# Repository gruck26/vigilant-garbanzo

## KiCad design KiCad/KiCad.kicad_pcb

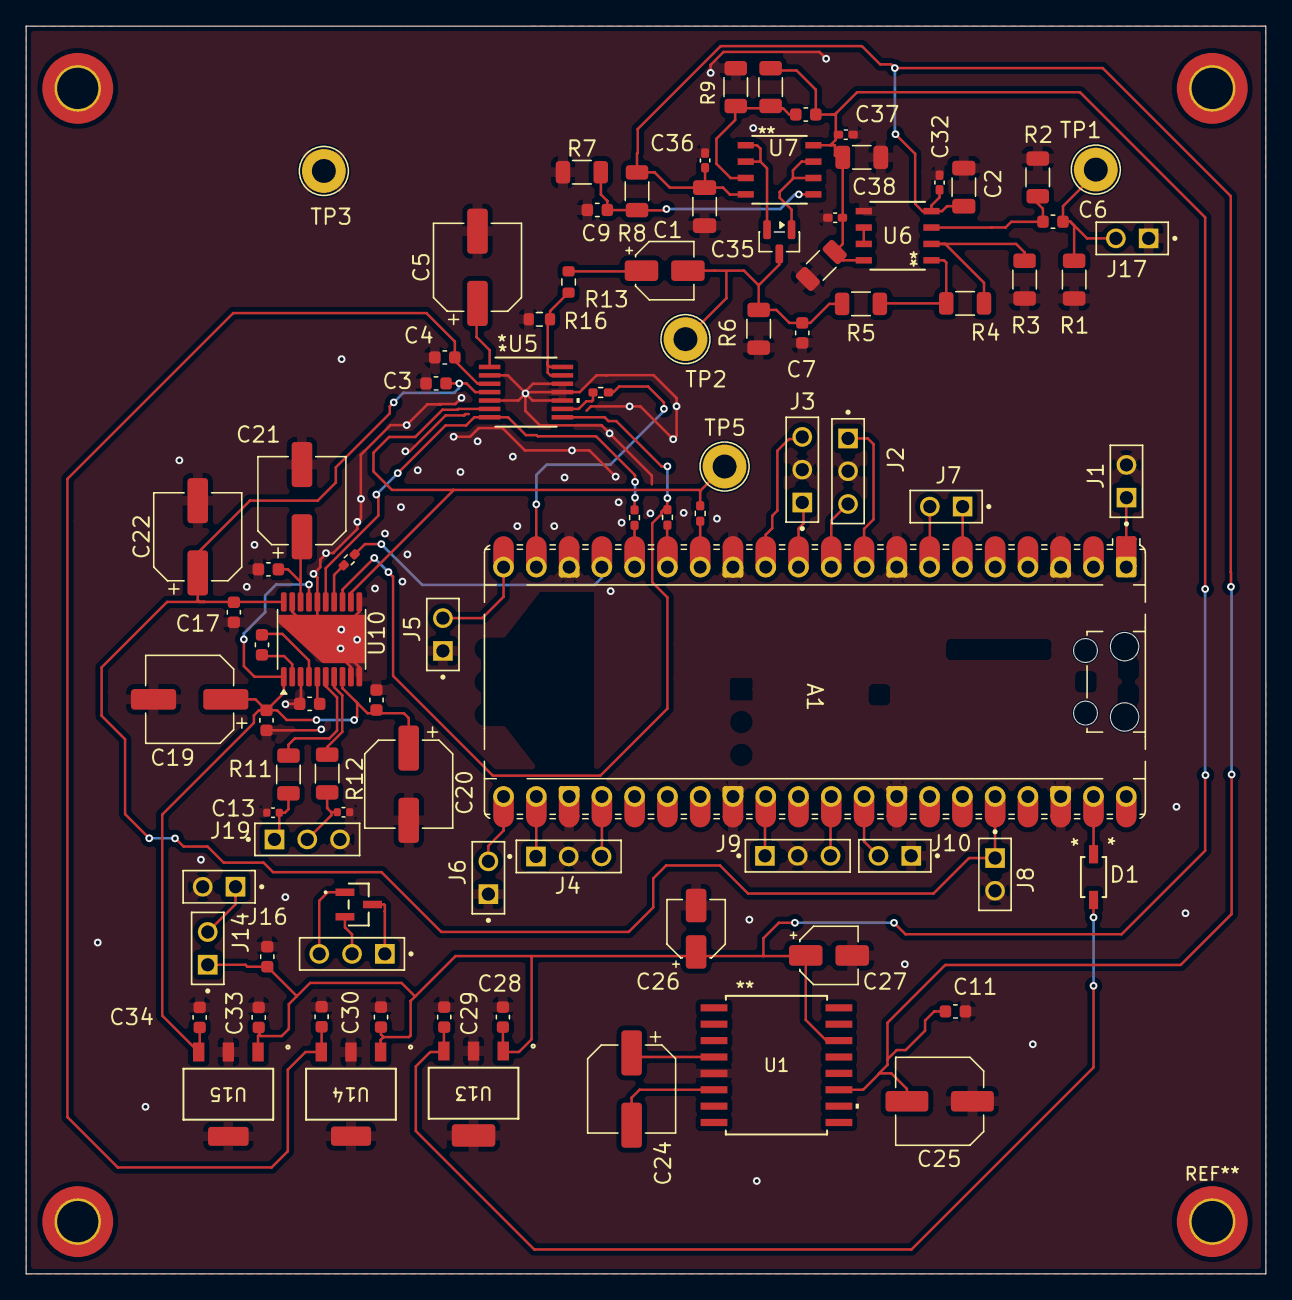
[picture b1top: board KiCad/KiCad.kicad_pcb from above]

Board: 2 copper layers, 96.1 x 96.7 mm, 90 parts (0 on the bottom side), 59 nets.

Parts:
A1: RaspberryPi_Pico; RaspberryPi_Pico_Common_Unspecified
C1, C26, C27: 1uF; CP_Elec_4x5.7
C2, C35, C38, C39: 10uF; C_1206_3216Metric
C3, C4, C6, C15, C16, C17, C18: 0.1uF; C_0603_1608Metric
C5, C19, C20, C21, C22, C24: 10uF; CP_Elec_6.3x5.4
C7: 33nF; C_0603_1608Metric
C8, C9, C28, C29, C30, C31, C33, C34: 1uF; C_0603_1608Metric
C10, C11: 10pF; C_0603_1608Metric
C12, C13: 2.2nF; C_0402_1005Metric
C14, C23: 2.2uF; C_0603_1608Metric
C25: 100uF; C_Elec_6.3x7.7
C32, C36, C37, C40: .1uF; C_0402_1005Metric_Pad0.74x0.62mm_HandSolder
D1: 1N5819; 1N5819HW-7-F_DIO-M
D2: BAT54S; SOT-23
J1, J7, J8: SSK02-FPH-254-A2; SAMESKY_SSK02-FPH-254-A2
J2, J3, J4, J9: SSK02-FPH-254-A3; SAMESKY_SSK02-FPH-254-A3
J5: footswitch1; SAMESKY_SSK02-FPH-254-A2
J6: footswitch2; SAMESKY_SSK02-FPH-254-A2
J10: footswitch3; SAMESKY_SSK02-FPH-254-A2
J14: powerRailAndBatteryGround; SAMESKY_SSK02-FPH-254-A2
J16: Barrel3andbarrel2; SAMESKY_SSK02-FPH-254-A2
J17: Guitar input; SAMESKY_SSK02-FPH-254-A2
J18, J19: positivePowerInputs; SAMESKY_SSK02-FPH-254-A3
R1: 1M; R_1206_3216Metric
R2: 22k; R_1206_3216Metric
R3: 47k; R_1206_3216Metric
R4, R6, R7, R9: 100k; R_1206_3216Metric
R5, R11, R12: 470; R_1206_3216Metric
R8, R10: 620k; R_1206_3216Metric
R13, R16: 0; R_0603_1608Metric
R14, R15, R17, R18, R19: 22; R_0402_1005Metric_Pad0.72x0.64mm_HandSolder
TP1, TP2, TP3, TP5: TestPoint; TestPoint_Loop_D2.50mm_Drill1.85mm
U1: LT1054CDWR; DW16-M
U2: PMEG2005CT_215; SOT_05CT215_NEX-M
U5: PCM1808-Q1_PW_14; PW14_TEX
U6, U7: NE5532; D8-L
U10: PCM5102APW; Texas_PW0020A_TSSOP-20_4.4x6.5mm_P0.65mm
U13, U14: MCP1703T-5002E/DB; SOT-223_3MC_MCH
U15: MCP1703T-3302E/DB; SOT-223_3MC_MCH

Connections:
+3.3VA: C15.1, C16.1, C19.1, C20.1, C34.1, U10.1 (CPVDD), U10.8 (AVDD), U10.17 (XSMT), U15.3 (VOUT)
+5VA: C4.2, C31.1, U5.3 (VCC), U14.3 (VOUT)
+5VD: C29.1, D1.2 (A), U13.3 (VOUT)
+9V: C8.1, C10.1, C26.1, C27.1, C28.1, C30.1, C33.1, C37.1, C38.2, C39.1, C40.2, J14.1, R10.2, U1.14 (VCC), U6.8 (V+), U7.8 (V+), U13.1 (VIN), U14.1 (VIN), U15.1 (VIN)
-9V: C2.2, C11.2, C25.2, C32.2, C35.1, C36.1, R8.2, U1.11 (VOUT), U6.4 (V-), U7.4 (V-)
/AnalogFE/Guitar_In: C6.1, J17.2, R1.1, TP1.1 (1_1)
ADC Din: A1.19 (GPIO14), R19.2
BCK: R15.2, U5.8 (BCK), U10.13 (BCK)
DAC Dout: A1.17 (GPIO13), R18.2
GND: A1.3 (GND), A1.8 (GND), A1.13 (GND), A1.18 (GND), A1.23 (GND), A1.28 (GND), A1.33 (AGND), A1.38 (GND), C2.1, C3.2, C4.1, C5.2, C7.2, C9.1, C10.2, C11.1, C12.2, C13.2, C15.2, C16.2, C17.2, C18.2, C19.2, C20.2, C21.2, C22.2, C23.2, C25.1, C26.2, C27.2, C28.2, C29.2, C30.2, C31.2, C32.1, C33.2, C34.2, C35.2, C36.2, C37.2, C38.1, C39.2, C40.1, J1.2, J2.2, J3.2, J4.2, J5.1, J6.1, J8.2, J9.2, J10.1, J16.2, J17.1, J19.3, R1.2, R2.1, R3.1, R6.2, R7.1, R9.1, R16.1, TP3.1 (1_1), U1.5 (GND), U5.2 (AGND), U5.5 (DGND), U5.10 (MD0), U5.11 (MD1), U5.12 (FMT), U6.5 (+), U10.3 (CPGND), U10.9 (AGND), U10.10 (DEMP), U10.11 (FLT), U10.16 (FMT), U10.19 (DGND), U13.2 (GND), U13.4, U14.2 (GND), U14.4, U15.2 (GND), U15.4
GPIO0: A1.1 (GPIO0), J1.1
GPIO4: A1.6 (GPIO4), J7.1
GPIO5: A1.7 (GPIO5), J7.2
GPIO6: A1.9 (GPIO6), J2.1
GPIO7: A1.10 (GPIO7), J2.3
GPIO8: A1.11 (GPIO8), J3.1
GPIO9: A1.12 (GPIO9), J3.3
GPIO15: A1.20 (GPIO15), J5.2
GPIO16: A1.21 (GPIO16), J6.2
GPIO17: A1.22 (GPIO17), J4.1
GPIO18: A1.24 (GPIO18), J4.3
GPIO22: A1.29 (GPIO22), J9.1
GPIO26: A1.31 (GPIO26_ADC0), J9.3
GPIO27: A1.32 (GPIO27_ADC1), J10.2
GuitarIn: C1.2, C7.1, D2.3 (COM), R5.2, R6.1, TP2.1 (1_1)
LRCK: R17.2, U5.7 (LRCK), U10.15 (LRCK)
MCK: R14.2, TP5.1 (1_1), U5.6 (SCKI), U10.12 (SCK)
unnamed: A1.14 (GPIO10), R14.1
unnamed: A1.15 (GPIO11), R15.1
unnamed: A1.16 (GPIO12), R17.1
unnamed: A1.39 (VSYS), D1.1 (K)
unnamed: C1.1, R13.2
unnamed: D2.1 (A), U7.6 (-), U7.7
unnamed: D2.2 (K), U7.1, U7.2 (-)
unnamed: J14.2, J16.1
unnamed: J18.2, U2.2 (anode)
unnamed: J18.3, U2.1 (anode)
unnamed: R4.2, R5.1, U6.1
unnamed: C24.1, U1.4 (CAP+)
unnamed: C24.2, U1.6 (CAP-)
unnamed: J18.1, U2.3 (common_cathode)
unnamed: R19.1, U5.9 (DOUT)
unnamed: R13.1, R16.2, U5.13 (VINL), U5.14 (VINR)
unnamed: C5.1, U5.1 (VREF)
unnamed: C6.2, R2.2, U6.3 (+)
unnamed: R3.2, R4.1, U6.2 (-)
unnamed: U6.6 (-), U6.7
unnamed: C8.2, R9.2, R10.1, U7.3 (+)
unnamed: C9.2, R7.2, R8.1, U7.5 (+)
unnamed: C14.2, U10.4 (CAPM)
unnamed: C14.1, U10.2 (CAPP)
unnamed: R18.1, U10.14 (DIN)
unnamed: C18.1, C21.1, U10.18 (LDOO)
unnamed: R11.1, U10.6 (OUTL)
unnamed: R12.1, U10.7 (OUTR)
unnamed: C23.1, U10.5 (VNEG)
SIG_L_OUT: C13.1, J19.1, R11.2
SIG_R_OUT: C12.1, J19.2, R12.2
Screen_Vcc: A1.36 (3V3), C3.1, C17.1, C22.1, J8.1, U5.4 (VDD), U10.20 (DVDD)

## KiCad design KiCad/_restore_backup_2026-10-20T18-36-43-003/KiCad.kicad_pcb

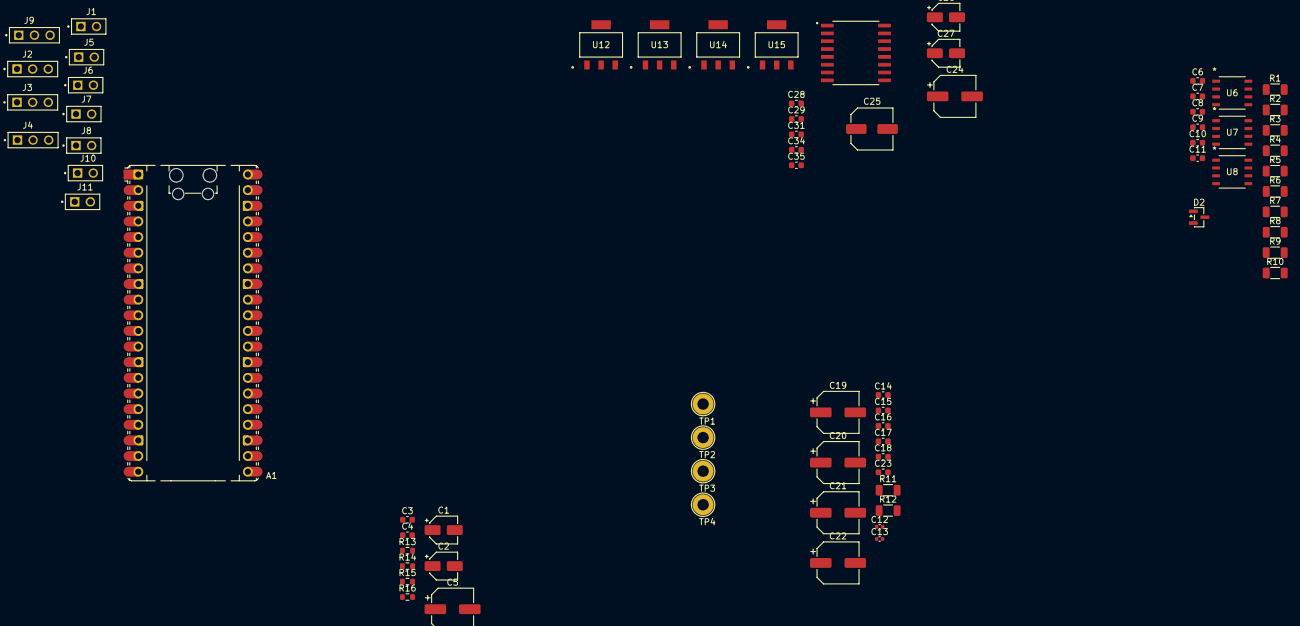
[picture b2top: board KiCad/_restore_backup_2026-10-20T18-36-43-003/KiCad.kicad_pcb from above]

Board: 2 copper layers, 73 parts (0 on the bottom side), 40 nets, no tracks yet.

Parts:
A1: RaspberryPi_Pico; RaspberryPi_Pico_Common_Unspecified
C1, C2, C26, C27: 1uF; CP_Elec_4x5.7
C3, C4, C6, C15, C16, C17, C18: 0.1uF; C_0603_1608Metric
C5, C19, C20, C21, C22, C24: 10uF; CP_Elec_6.3x5.4
C7: 33nF; C_0603_1608Metric
C8, C9, C28, C29, C31, C34, C35: 1uF; C_0603_1608Metric
C10, C11: 10pF; C_0603_1608Metric
C12, C13: 2.2nF; C_0402_1005Metric
C14, C23: 2.2uF; C_0603_1608Metric
C25: 100uF; C_Elec_6.3x7.7
D2: BAT54S; SOT-23
J1, J5, J6, J7, J8, J10, J11: SSK02-FPH-254-A2; SAMESKY_SSK02-FPH-254-A2
J2, J3, J4, J9: SSK02-FPH-254-A3; SAMESKY_SSK02-FPH-254-A3
R1: 1M; R_1206_3216Metric
R2: 22k; R_1206_3216Metric
R3: 47k; R_1206_3216Metric
R4, R6, R7, R9: 100k; R_1206_3216Metric
R5, R11, R12: 470; R_1206_3216Metric
R8, R10: 620k; R_1206_3216Metric
R13, R14, R15, R16: 0; R_0603_1608Metric
TP1, TP2, TP3, TP4: TestPoint; TestPoint_Loop_D2.50mm_Drill1.85mm
U1: LT1054; SOIC127P1030X265-16N
U6, U7, U8: NE5532; D8-L
U12, U15: MCP1703T-3302E/DB; SOT-223_3MC_MCH
U13, U14: MCP1703T-5002E/DB; SOT-223_3MC_MCH

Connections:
+3.3V: C35.1, U12.3 (VOUT)
+3.3VA: C15.1, C16.1, C19.1, C20.1, C34.1, U15.3 (VOUT)
+3V3: C3.1, C17.1, C22.1
+5VA: C4.2, C31.1, U14.3 (VOUT)
+5VD: C29.1, U13.3 (VOUT)
+9V: C8.1, C10.1, C26.1, C27.1, C28.1, R9.2, U1.8 (V+), U12.1 (VIN), U13.1 (VIN), U14.1 (VIN), U15.1 (VIN)
-9V: C11.2, C25.2, R8.2, U1.5 (-VOUT)
/AnalogFE/Guitar_In: C6.1, R1.1
GND: C3.2, C5.2, C7.2, C9.1, C10.2, C11.1, C17.2, C18.2, C21.2, C22.2, C25.1, C26.2, C27.2, C28.2, C29.2, C31.2, C34.2, C35.2, J1.2, J2.2, J3.2, J4.2, J5.1, J6.1, J8.2, J9.2, R1.2, R2.1, R3.1, R6.2, R7.1, R10.1, U1.3 (GND), U12.2 (GND), U13.2 (GND), U14.2 (GND), U15.2 (GND)
GNDA: C4.1, C12.2, C13.2, C15.2, C16.2, C19.2, C20.2, C23.2, R15.1, R16.1
GPIO0: A1.1 (GPIO0), J5.2
GPIO1: A1.2 (GPIO1), J6.2
GPIO4: A1.6 (GPIO4), J7.2
GPIO5: A1.7 (GPIO5), J7.1
GPIO6: A1.9 (GPIO6), J9.1
GPIO7: A1.10 (GPIO7), J9.3
GPIO8: A1.11 (GPIO8), J2.1
GPIO9: A1.12 (GPIO9), J2.3
GPIO15: A1.20 (GPIO15), J3.1
GPIO16: A1.21 (GPIO16), J3.3
GPIO17: A1.22 (GPIO17), J4.1
GPIO18: A1.24 (GPIO18), J4.3
GPIO28: A1.34 (GPIO28_ADC2), J1.1
unnamed: C1.1, R13.2
unnamed: C2.1, R14.2
unnamed: D2.1 (A), TP3.1 (1_1), U8.1, U8.2 (-)
unnamed: C7.1, D2.3 (COM), R5.2, R6.1, TP2.1 (1_1)
unnamed: D2.2 (K), TP1.1 (1_1), U7.1, U7.2 (-)
unnamed: R4.2, R5.1, TP4.1 (1_1), U6.1
unnamed: C24.1, U1.2 (CAP+)
unnamed: C24.2, U1.4 (CAP-)
unnamed: R14.1, R15.2
unnamed: R13.1, R16.2
unnamed: C6.2, R2.2, U6.3 (+)
unnamed: R3.2, R4.1, U6.2 (-)
unnamed: C8.2, R9.1, R10.2, U7.3 (+)
unnamed: C9.2, R7.2, R8.1, U8.3 (+)
unnamed: C18.1, C21.1
SIG_L_OUT: C13.1, R11.2
SIG_R_OUT: C12.1, R12.2

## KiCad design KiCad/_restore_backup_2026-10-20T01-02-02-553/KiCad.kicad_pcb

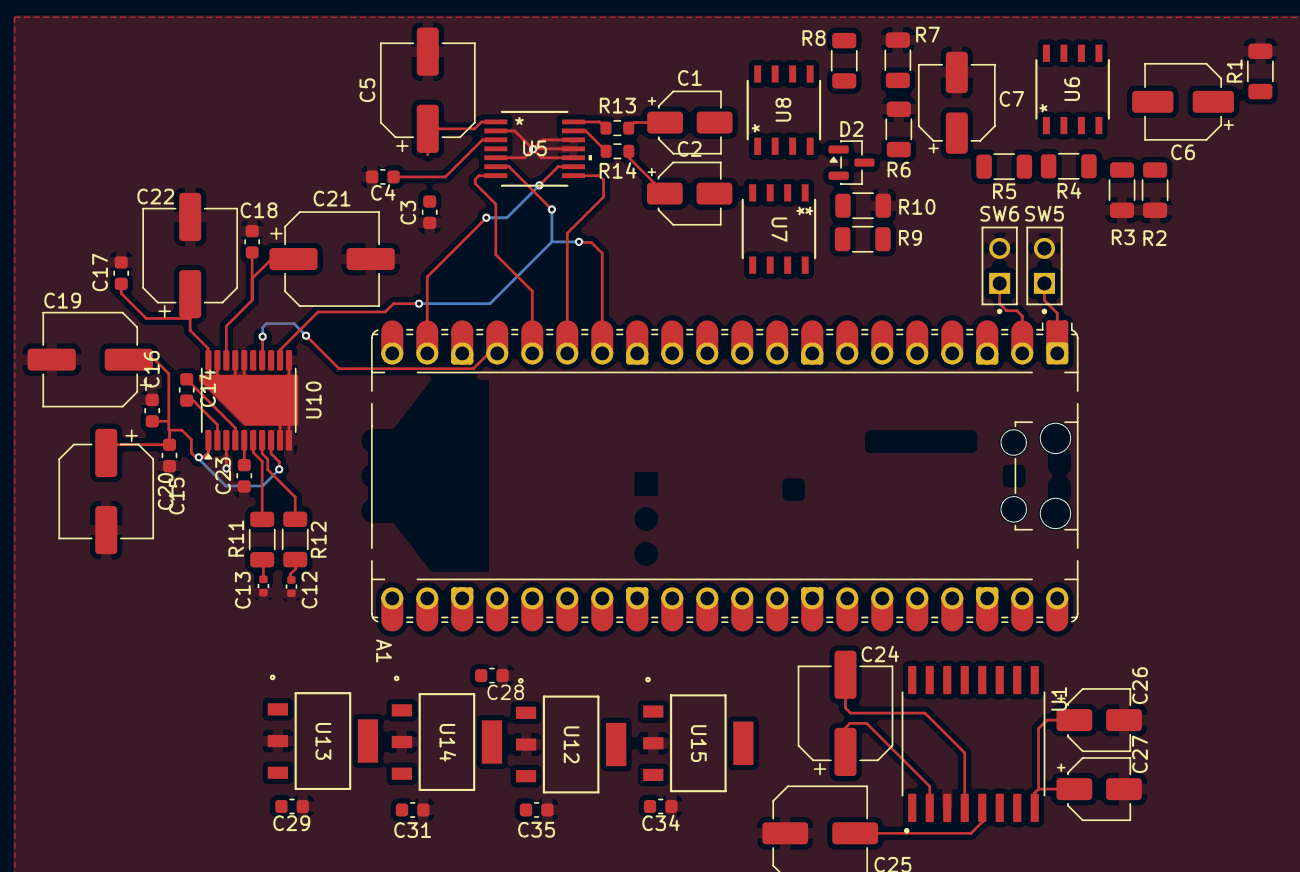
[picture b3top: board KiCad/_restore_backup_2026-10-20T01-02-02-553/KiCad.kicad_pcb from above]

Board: 2 copper layers, 56 parts (0 on the bottom side), 37 nets.

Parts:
A1: RaspberryPi_Pico; RaspberryPi_Pico_Common_Unspecified
C1, C2, C26, C27: 1uF; CP_Elec_4x5.7
C3, C4, C15, C16, C17, C18: 0.1uF; C_0603_1608Metric
C5, C19, C20, C21, C22, C24: 10uF; CP_Elec_6.3x5.4
C6: 0.1uF; CP_Elec_5x4.5
C7: 33nF; CP_Elec_5x4.5
C12, C13: 2.2nF; C_0402_1005Metric
C14, C23: 2.2uF; C_0603_1608Metric
C25: 100uF; C_Elec_6.3x7.7
C28, C29, C31, C34, C35: 1uF; C_0603_1608Metric
D2: BAT54S; SOT-23
R1: 1M; R_1206_3216Metric
R2: 22k; R_1206_3216Metric
R3: 47k; R_1206_3216Metric
R4, R6, R7, R9: 100k; R_1206_3216Metric
R5, R11, R12: 470; R_1206_3216Metric
R8, R10: 620k; R_1206_3216Metric
R13, R14: 0; R_0603_1608Metric
SW5, SW6: SAMESKY_SSK02-FPH-254-A2
U1: LT1054; SOIC127P1030X265-16N
U5: PCM1808-Q1_PW_14; PW14_TEX
U6, U7, U8: NE5532; D8-L
U10: PCM5102APW; Texas_PW0020A_TSSOP-20_4.4x6.5mm_P0.65mm
U12, U15: MCP1703T-3302E/DB; SOT-223_3MC_MCH
U13, U14: MCP1703T-5002E/DB; SOT-223_3MC_MCH

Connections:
+3.3V: C35.1, U12.3 (VOUT)
+3.3VA: C15.1, C16.1, C19.1, C20.1, C34.1, U10.1 (CPVDD), U10.8 (AVDD), U15.3 (VOUT)
+3V3: C3.1, C17.1, C22.1, U5.4 (VDD), U10.20 (DVDD)
+5VA: C4.2, C31.1, U5.3 (VCC), U14.3 (VOUT)
+5VD: C29.1, U13.3 (VOUT)
+9V: C26.1, C27.1, C28.1, R9.2, U1.8 (V+), U12.1 (VIN), U13.1 (VIN), U14.1 (VIN), U15.1 (VIN)
-9V: C25.2, R8.2, U1.5 (-VOUT)
/AnalogFE/Guitar_In: C6.1, R1.1
ADC Din: A1.19 (GPIO14), U5.9 (DOUT)
BCK: A1.15 (GPIO11), U5.8 (BCK), U10.13 (BCK)
DAC Dout: A1.17 (GPIO13), U10.14 (DIN)
GND: C3.2, C4.1, C5.2, C7.2, C12.2, C13.2, C15.2, C16.2, C17.2, C18.2, C19.2, C20.2, C21.2, C22.2, C23.2, C25.1, C26.2, C27.2, C28.2, C29.2, C31.2, C34.2, C35.2, R1.2, R2.1, R3.1, R6.2, R7.1, R10.1, SW5.2, SW6.2, U1.3 (GND), U5.2 (AGND), U5.5 (DGND), U5.10 (MD0), U5.11 (MD1), U5.12 (FMT), U10.3 (CPGND), U10.9 (AGND), U10.10 (DEMP), U10.11 (FLT), U10.16 (FMT), U10.17 (XSMT), U10.19 (DGND), U12.2 (GND), U13.2 (GND), U14.2 (GND), U15.2 (GND)
LRCK: A1.16 (GPIO12), U5.7 (LRCK), U10.15 (LRCK)
MCK: A1.14 (GPIO10), U5.6 (SCKI), U10.12 (SCK)
unnamed: C1.1, R13.2
unnamed: C2.1, R14.2
unnamed: D2.1 (A), U8.1, U8.2 (-)
unnamed: C7.1, D2.3 (COM), R5.2, R6.1
unnamed: D2.2 (K), U7.1, U7.2 (-)
unnamed: R4.2, R5.1, U6.1
unnamed: C24.1, U1.2 (CAP+)
unnamed: C24.2, U1.4 (CAP-)
unnamed: R14.1, U5.13 (VINL)
unnamed: R13.1, U5.14 (VINR)
unnamed: C5.1, U5.1 (VREF)
unnamed: C6.2, R2.2, U6.3 (+)
unnamed: R3.2, R4.1, U6.2 (-)
unnamed: R9.1, R10.2, U7.3 (+)
unnamed: R7.2, R8.1, U8.3 (+)
unnamed: C14.2, U10.4 (CAPM)
unnamed: C14.1, U10.2 (CAPP)
unnamed: C18.1, C21.1, U10.18 (LDOO)
unnamed: R11.1, U10.6 (OUTL)
unnamed: R12.1, U10.7 (OUTR)
unnamed: C23.1, U10.5 (VNEG)
SIG_L_OUT: C13.1, R11.2
SIG_R_OUT: C12.1, R12.2
